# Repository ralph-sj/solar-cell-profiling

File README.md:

# solar-cell-profiling using a low power micro-computer
Hardware and software for power profiling a solar cell over a range of irradiances using cheap/easy to use hardware and software e.g. low power ADC/op-amps and raspberry pi/arduino 

## Introduction

A raspberry pi can be set up to measure voltages over time as a simple datalogger.  An ADC is connected to the IO pins of the pi and configured to take measurements and return the data to the Pi.  Data can then be sent to a remote server or stored locally or processed further.

## Guides
Mathworks [1] have a simple tutorial for setting this up with an LCD screen.	This uses the MCP3004 ADC [2] connected to the raspberry pi.

## Impedance
The input impedance of the ADC determines the current sunk by the ADC from the source which it is measuring.  When the input impedance is low compared to the output impedance of the source then there will be a voltage drop due to the ADC sinking current.  There are guides that show examples of this and address ways to counter it [3,4].	

## Hardware

The hardware used here is selected for ease of use and availability, including the procesor, sensors and other peripherals. It consists of: 
- MSP430G2553 Launchpad.  This is the demo board for the G2553 variant of the popular MSP430 MCU.
- LT1920 instrumentation amplifier.

### MCU
### Trans-Impedance Amplifier
This is used decrease the voltage drop imposed by the use of an ammeter in series within the monitoring circuit.  This allows a 1 Ohmm resistor to be used rather than the higher burden 1k.  As the currents measured here are typically low (uA - mA), to e.g. resolve a 1uA current without gain (i.e. to convert a 1uA current to 1mA - the maximum resolution of the 10-bit ADC used with a 1V reference) a 1K resistor would be needed.  This would then drop the voltage in the circuit by that amount.  By using a 1 Ohm resistor, that burden is reduced to an almost immeasurable 1 uA ^[11].  The burden voltage is 10µV/µA and 10µV/nA on the lower ranges and varies on the mA range due to the switch resistance.  

**Ranges:**

- Current ranges:
    1. +/- 0-300mA (70µV / mA burden voltage typical) - max 21mV
    2. +/- 0-1000µA (10µV / uA burden voltage) - max 10 mV
    3. +/- 0-1000nA (10µV / nA burden voltage) - max 10 mV
- Output Voltage Units:
    1. 1mV/mA - max 3V
    2. 1mV/µA - max 1V
    3. 1mV/nA - max 1V
- Effective gain 100 (I think)

### Instrumentation amplifier
The **LT2910** instrumentation amplifier is used to amplify the signal from the trans-impedance amplifier.  The gain is variable from 1 to 10,00 and is determined by the value of the gain resistor, RG, connected across pins 1-8.  The gain for a given value of RG is given by
G = 1 + 49.4/RG
i.e. for the following gain values:
Gain = 1000, RG = 49.4 Ohms
Gain = 100, RG = 499 Ohms
Gain = 10, RG = 5.489 kOhms

An alternative is the AD8428 ^[6] which has a fixed gain of 2000

## Software
Simpel software running on a low power procesosr is to be created to read sensors and then save data in a remote server. It is designed to run on  the MSP-EXP430G2 launchpad ^[7],[8],[10].  This is used due to their availability, ease of use and low power operation
 
### Development environment
The Arduino-like Energia ^[9] development environment was used here due to the ease of use and the widespread availability of libraries.

## References
[1](http://makerzone.mathworks.com/resources/build-a-digital-voltmeter-using-raspberry-pi/) Mathworks, "Build a Digital Voltmeter Using Raspberry Pi" (2005)
[2](https://cdn-shop.adafruit.com/datasheets/MCP3008.pdf), Microchip, MCP3004 Datasheet (2008)
[3](http://www.ti.com/lit/an/spna088/spna088.pdf)
[4](http://www.ti.com/lit/an/sbaa090/sbaa090.pdf)
[5](http://cds.linear.com/docs/en/datasheet/1920f.pdf), LT21920 Datasheet
[6](http://www.analog.com/media/en/technical-documentation/data-sheets/AD8428.PDF), AD8428
[7](http://www.ti.com/tool/MSP-EXP430G2), MSP-EXP430G2 homepage
[9](http://energia.nu/pin-maps/guide_msp430g2launchpad/), Energia for launchpad
[10](http://www.ti.com/lsds/ti/tools-software/launchpads/launchpads.page), TI Launchpad Homepage
[11](http://alternatezone.com/electronics/ucurrent/uCurrentArticle.pdf), uCurrent infor sheet

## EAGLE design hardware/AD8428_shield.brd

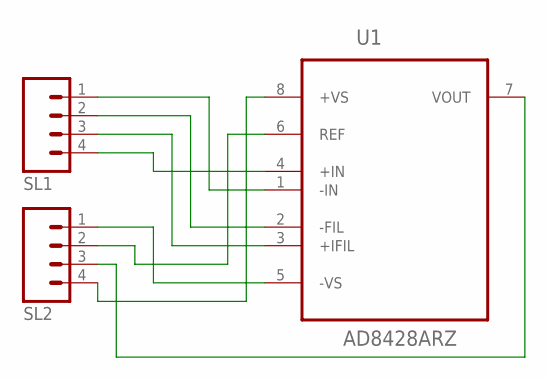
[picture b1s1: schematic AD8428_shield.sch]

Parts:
SL1, SL2: M04; 04P
U1: AD8428ARZ; SOIC127P600X175-8N

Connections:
unnamed: SL1.1, U1.1 (-IN)
unnamed: SL1.2, U1.2 (-FIL)
unnamed: SL1.3, U1.3 (+IFIL)
unnamed: SL1.4, U1.4 (+IN)
unnamed: SL2.1, U1.5 (-VS)
unnamed: SL2.2, U1.6 (REF)
unnamed: SL2.3, U1.7 (VOUT)
unnamed: SL2.4, U1.8 (+VS)

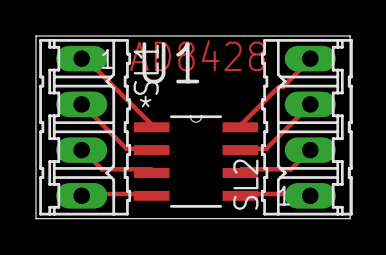
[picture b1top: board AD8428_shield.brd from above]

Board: 2 copper layers, 17.4 x 10.2 mm, 3 parts (0 on the bottom side), 8 nets.

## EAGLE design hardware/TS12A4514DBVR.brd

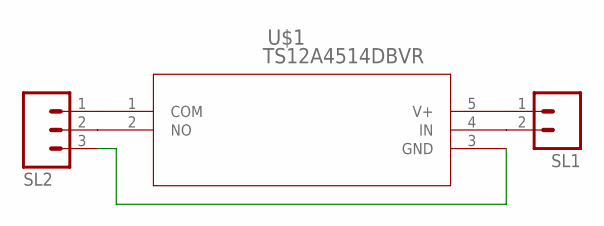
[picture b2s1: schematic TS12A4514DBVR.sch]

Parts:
SL1: M02; 02P
SL2: M03; 03P
U$1: TS12A4514DBVR; DBV5

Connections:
unnamed: SL1.1, U$1.5 (V+)
unnamed: SL1.2, U$1.4 (IN)
unnamed: SL2.1, U$1.1 (COM)
unnamed: SL2.2, U$1.2 (NO)
unnamed: SL2.3, U$1.3 (GND)

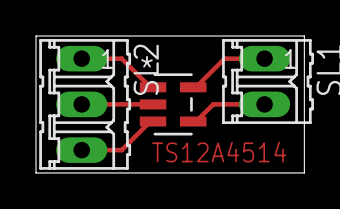
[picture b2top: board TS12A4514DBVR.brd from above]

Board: 2 copper layers, 14.9 x 7.6 mm, 3 parts (0 on the bottom side), 5 nets.

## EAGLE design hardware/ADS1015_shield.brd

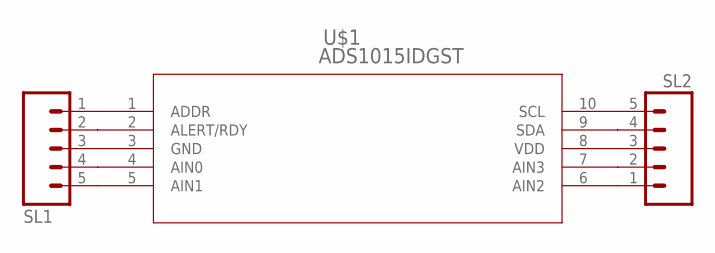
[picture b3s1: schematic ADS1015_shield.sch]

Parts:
SL1, SL2: M05; 05P
U$1: ADS1015IDGST; DGS10

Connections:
unnamed: SL1.1, U$1.1 (ADDR)
unnamed: SL1.2, U$1.2 (ALERT/RDY)
unnamed: SL1.3, U$1.3 (GND)
unnamed: SL1.4, U$1.4 (AIN0)
unnamed: SL1.5, U$1.5 (AIN1)
unnamed: SL2.1, U$1.6 (AIN2)
unnamed: SL2.2, U$1.7 (AIN3)
unnamed: SL2.3, U$1.8 (VDD)
unnamed: SL2.4, U$1.9 (SDA)
unnamed: SL2.5, U$1.10 (SCL)

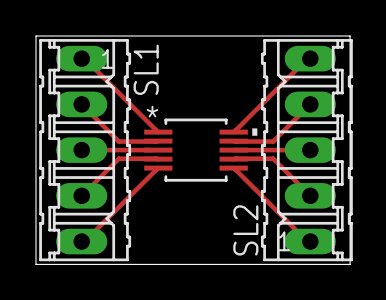
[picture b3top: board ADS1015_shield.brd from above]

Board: 2 copper layers, 17.4 x 12.7 mm, 3 parts (0 on the bottom side), 10 nets.

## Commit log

2016-10-31 added parts spreadsheet
2016-11-01 hardware/software folders created pats spreadsheet moved # Please enter the commit message for your changes. Lines starting # with '#' will be ignored, and an empty message aborts the commit. # On br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
2016-11-01 - updated parts list
    ordered components
2016-11-10 - added ADC and inst. amp shields
    added shields for AD8428 inst amp (set gain 2000) and ADS1015 12 bit ADC
2016-11-10 - added data sheets
    - added data sheets to folder and to README
2016-11-10 updated AD8428 shield
    - added text to board
2016-11-10 added TS12A4514 datasheet
2016-11-11 - updated spelling
2016-11-11 Added uCurrent files
    Added design/information files regarding uCurrent current amplifier circuit.
2016-11-11 Added software
    Added Launchpad Energia programme, read-light-current.ino to software folder
2016-11-14 Added ADS1115 datasheets
    Added datasheet and adafruit guide to repo
2016-11-14 created altium files
    converted eagle-altium file for AD8428 board
2016-11-14 added altium PCBs
    converted ADS1015 board eagle-altium
2016-11-14 added altium PCB
    Converted TS12A4514 shield PCB eagle-altium
2016-11-14 Created zip file for altium PCB
    - added all alitum PCB files to zip file for sending to mnfctr
2016-11-14 added ADS1x15 software
    - added adafruit ADS1x15 (arduino) library
    - added example code from (arduino) examples
2016-11-14 updated read-light-current
    - renamed address character
2016-11-15 added ADS1115 code arduino
    added arduino example code for reading 1 channel using adafruit library
2016-11-15 arduino test
    - added .ino file for testing Arduino
    - added test data for ADC calibration
2016-11-15 updated Arduino code
    - reconfigured for ADS1115
    - updated range of DAC for test
2016-11-15 updated ads1115 test data
    - added test with differential input, single-ended with potentiometer
2016-11-16 added test data
    added test data spreadsheets with initial power profiles of a selection of solar cells
2016-11-16 reconfigured arduino code layout
    moved arduino code to new folder
    updated arduino software for running power profile
2016-11-16 Added matlab code for processing of test data.
    Code takes text or excel files, read in data and plots graphs
2016-11-17 Updated Matlab script
    - updated matlab data analysis script to load file name from overnight test and next day test. This reads in the time stamp (matlab format) from the data file in the first column.
2016-11-21 Added matlab file for reading file with title
    Matlabe reads files as per 21/11/2016 file format
2016-11-21 updated matlabe cuurent plotter
    updated file to plot
    changed plot type to line
2016-11-21 updated arduino program
    changed gain settings for current and voltage
    changed initial splurge output
    input switch statement for setting current gain
    changed voltage rang to +/- 2V
    changed current range to +/i 0.256V (i.e. +/- 256 uA with middle uCurrent gain setting)
2016-11-21 added bouds test matlab code
    added program for splitting and averaging intervals within light levels
2016-11-21 amended bounds_test.m
    updated upper and lower bounds :
2016-11-21 created copy of read data file
    copy created to read new files while other is in use by the office PC to read in data and plot
2016-11-22 Added bounds_test.m
    this separates light range into sections and calculates the average for each section
2016-11-22 Added new file link to read_photo_current_with_title
    added compatability with new solar cell
2016-11-22 Added support for changing gain of ADC
    gain can be selected as 2,4,8,16
2016-11-22 updated bound_test
    correct calcualtion of upper and lower bounds
2016-11-22 updated read_photo_current_with_title.m
    - changed to file selction by name c.f. full path
    - corrected current unit to uA and power units, uW, for graph labelling
    - added title to final graph with filename
2016-11-22 changed current gain
    set to 8 for AM-1417CA solar cell
2016-11-23 matlab files moved to analysis folder
2016-11-23 matlabe files moved to analysis folder
2016-11-23 matlab figure processing added
    added file links to new solar cells
    added script for saving figures to images folder
2016-11-23 added solar cell info spreadsheet
    spreadsheet contains summary of information on solar cell used (size, part no, datasheets)
2016-11-23 amended matlab read function
    - updated links to files
2016-11-24 updated matlab figure plotter
    reformatted figures
    removed impedance plot
    added time/power plot
    added support for new (23/11/2016) solar cell (AM-5412CAR)
2016-11-24 added support for OS to read file
    automatically select OS using iscp/ismac functions
    added support for newer files
2016-11-24 updated bounds_test
    changed calculation of midpoints to midpoints of each data range c.f.
    average of all values
    included code to save summarised light and power light and power values
    to .mat files with the name of the file in the workspace
2016-11-24 added process_data M script
    script added for processing all solar cell data and creating plot with
    all data
2016-11-24 updated read_photo_current_with_title M script
    updated to run with process_data.m - do not clear file or file script
    variables
    added display of end time
2016-11-24 added find_outliers.m
    script for finding outlining data points from graph
2016-11-24 added summarised data from solar cells
    .at files containing summarised power and light arrays for each solar
    cell in the format:
    l_av, p_av
    …, …
    generated from bounds_test.m
2016-11-24 updated matlab script and arduino code, added solar cell.xlsx

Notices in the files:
parts and their libraries:
COPYRIGHT: Copyright C 2015 Accelerated Designs. All rights reserved
